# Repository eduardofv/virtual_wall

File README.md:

# Roomba-like Virtual Wall

## Description

This is an old project that I've been using at home for a couple of years. Sorry for not having all the references I originally used to develop this, I'll try to update as soon as possible.

Many of this things are pretty rough, specially the PCB and the 3D printed enclosure as it was my first model. Hope this can help anyone interested.

- Arduino based code for ATTiny85 controller, a IR Led and a standard white led for status
- Used a MT3608 voltage booster and 2 or 3 AA/AAA batteries
- PCB dessigned with Freecad, DIYed at home (2.5x5cm copper PBC)
- Programmed the uC with Arduino (1.8+) IDE. Download libraries for ATT85. Use Arduino UNO as ISP to program. Check references in code
- Enclosure designed in Blender and 3D printed on a Monoprice Select Mini v2 with black PLA

## TODO:

- Correct PCB wiring for LED Pin - checar en el prototipo 2
- Eliminar el algoritmo del led para indicar nivel de batería - no funciona bien
- Generar nueva version (v3)
- Documento de descripción del proyecto, referencias a proyectos originales
- Fotos / Video

## Changelog

- 2022-12-27:  New version with no VDC monitoring. Uses TP4056 + 18650 battery
- Started 2020
## Resources

-

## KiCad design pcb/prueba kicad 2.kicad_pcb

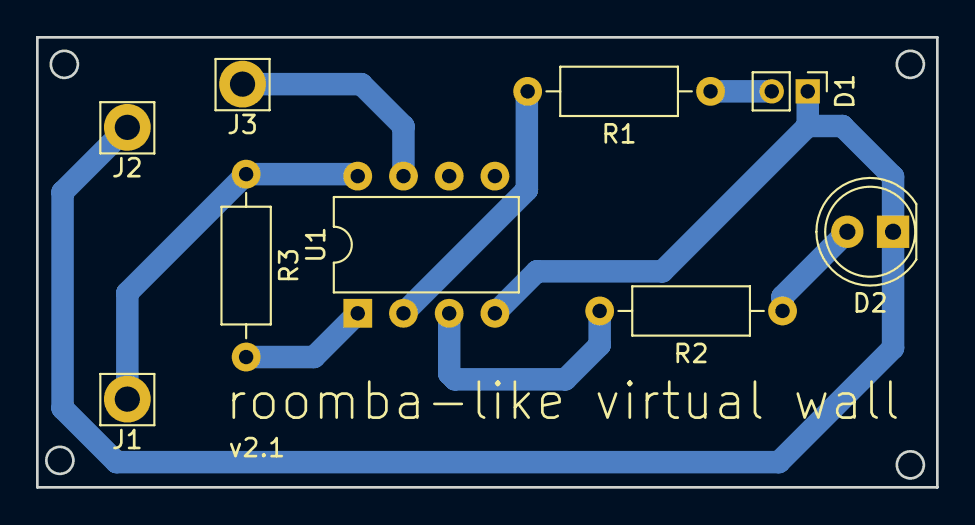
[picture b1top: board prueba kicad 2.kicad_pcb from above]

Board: 2 copper layers, 50.0 x 25.0 mm, 9 parts (0 on the bottom side), 8 nets.

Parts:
D1: LED; PinHeader_1x02_P2.00mm_Vertical
D2: IR LED; LED_D5.0mm
J1: +5V; Pin_D1.4mm_L8.5mm_W2.8mm_FlatFork
J2: GND; Pin_D1.4mm_L8.5mm_W2.8mm_FlatFork
J3: Battery Level; Pin_D1.4mm_L8.5mm_W2.8mm_FlatFork
R1: 2.2K; R_Axial_DIN0207_L6.3mm_D2.5mm_P10.16mm_Horizontal
R2: 47; R_Axial_DIN0207_L6.3mm_D2.5mm_P10.16mm_Horizontal
R3: 10K; R_Axial_DIN0207_L6.3mm_D2.5mm_P10.16mm_Horizontal
U1: ATtiny85-20PU; DIP-8_W7.62mm

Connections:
+5V: J1.1, R3.1, U1.8
GND: D1.1, D2.1, J2.1, U1.4
unnamed: D1.2, R1.1
unnamed: D2.2, R2.1
unnamed: J3.1, U1.7
unnamed: R1.2, U1.2
unnamed: R2.2, U1.3
unnamed: R3.2, U1.1

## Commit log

2022-07-13 Carga inicial
2022-07-13 New feature: shutdown after 2 hours
2022-07-14 Updated timer shutdown
2022-07-14 Organized 3D files
2022-07-14 Added comments and TODO. Ignore vim's swap file
2022-07-14 Better intro to the project
2022-07-14 Deleted useless file
2022-07-14 Corrected type bugs in timeout for shutdown
2022-07-14 Corrected type bugs in timeout for shutdown - prod version
2022-12-27 Arreglar primer virtual wall que se echó la Trufa
2022-12-27 Update para versión de KiCAD
